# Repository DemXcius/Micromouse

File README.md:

# Micromouse
# The repository for a third-year engineering design project
This repository contains the design and production files for the Power and Sensor modules of a micro-mouse, as part of the EEE3088F course at UCT 2024 Main Project.

# Project Overview: Micro-Mouse Hardware Design

## What is a Micro-Mouse?
In essence, a micro-mouse is a maze-solving robot. If you're unfamiliar with the concept, watch [Veritasium's](https://www.youtube.com/watch?v=ZMQbHMgK2rw) video to gain a clearer understanding. It's worth noting that while the robots featured in the video may be quite speedy, this micro-mouse will likely (almost certainly) operate at a slower pace. Nonetheless, let the video serve as inspiration.

## Project Description
This project focuses primarily on the design of the micro-mouse's hardware, with some minor software components. The main challenge lies in meeting the project's requirements while adhering to a STRICT budget. To facilitate this endeavor, the project has been divided into four modules: the processor, motherboard, sensing, and power.
The processor and motherboard modules have already been designed and this repository focuses only on the sensing and power modules. 

## Project Modules

### Processor Module: 
This module entails the design of the microcontroller unit responsible for controlling the micro-mouse's actions within the maze. The processor used is an STM32L476.

### Motherboard Module: 
The motherboard serves as the central hub for connecting various hardware components of the micro-mouse. Here, there is leeway as to how the motherboard is designed.

### Sensing Module: 
The project will involve designing and manufacturing the sensing module, which comprises sensors responsible for detecting walls, corners, and other obstacles within the maze.

### Power Module: 
Lastly, the project involves designing and manufacturing the power module, which will provide the necessary electrical power to all components of the micro-mouse.

## Budget Constraint
It's crucial to note that this project had a strict budget constraint imposed. While innovation and creativity are encouraged, all design decisions were made with the budget in mind.

## Project Details:
- Project Focus: Power and sensing module design and manufacturing.
- Connectors: JST PH 2mm pin pitch connector for the battery and a 2x8 (2.54mm pin pitch) pin header for interfacing with the motherboard.
- Budget: $8.25 per board.

## Subsystem Description: Power
- Motor Operation: Controls 2 motors, each capable of drawing up to 200mA, powered by a 1S1P battery.
- Battery Voltage Sensing: Provides an analog connection to sense battery voltage for battery state of charge (SoC) monitoring.
- Battery Charging: Charges the battery from the 5V input pin. Must handle the scenario when 5V is removed.
- ON/OFF Switch: Incorporates an ON/OFF switch with specific power consumption requirements in the OFF and ON states.
  
## Subsystem Description: Sensing
- Sensor Operation: Detects whether there is an obstacle in front of the robot or on its sides.
- Power Saving: Has switching means to save power when not in operation.
- Main Components: 4x TSAL4400 IR LED's, 3x SFH205F photodiodes, 1x LiPo 800mAh 3.7V

- ## Included Files:
- Datasheets: Datasheets for components used in the Power and Sensing modules.
- Production Files: Files required for manufacturing the Power and Sensing module, including Gerber files and Bill of Materials (BOM).
- Schematics: Schematics for Power and Sensing modules.
  
## Usage:
- Clone the repository to access all project files.
- Review the datasheets for component specifications.
- Use the production files for manufacturing the Power or Sensing module PCB's.
- Review and modify the PCB files as needed for customization.
  
- NOTE: Production and files associated with the production were designed and used with [jlcpcb](https://jlcpcb.com/) as the manufacturer in mind.

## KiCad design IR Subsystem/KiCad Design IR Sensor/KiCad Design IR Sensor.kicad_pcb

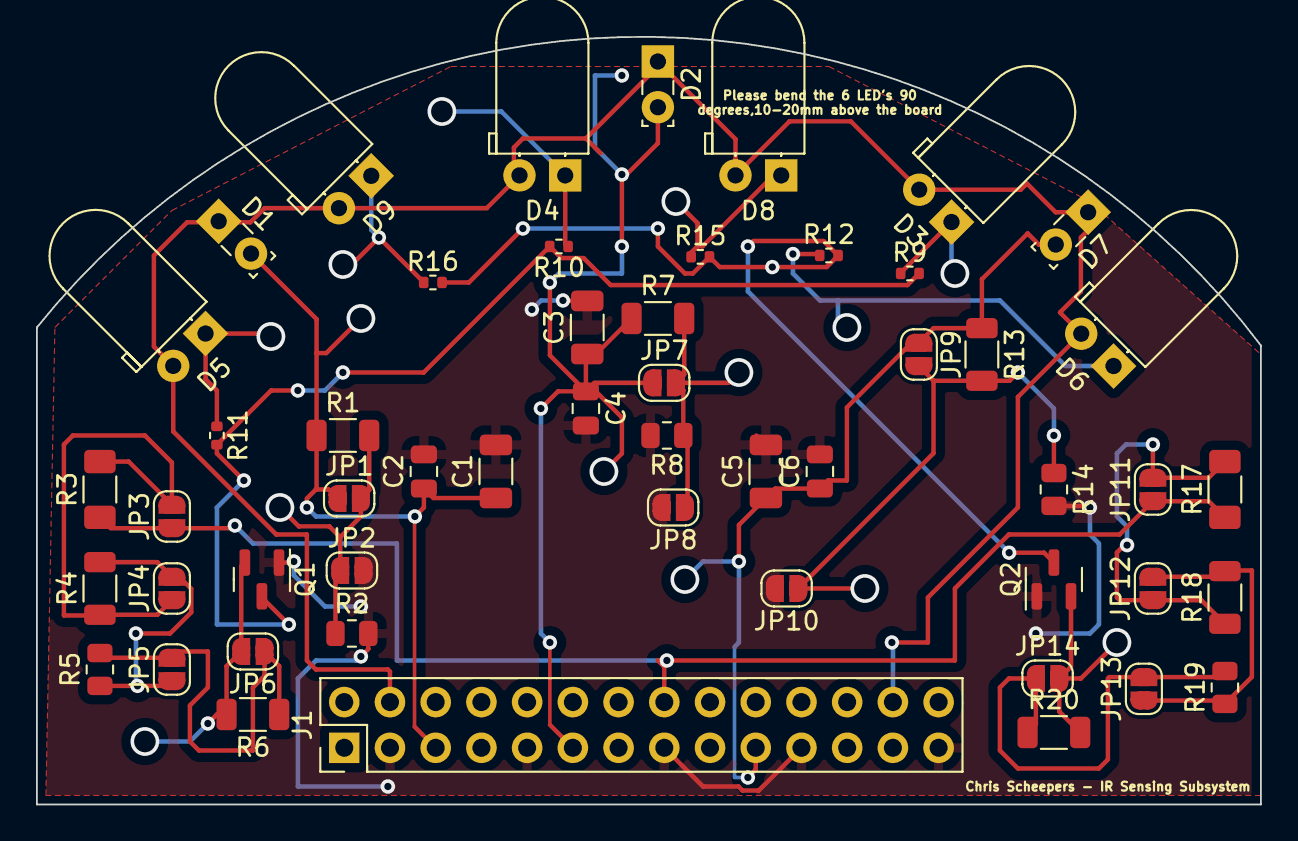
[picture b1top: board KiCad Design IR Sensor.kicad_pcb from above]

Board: 2 copper layers, 68.0 x 42.6 mm, 52 parts (0 on the bottom side), 25 nets.

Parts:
C1, C3, C5: 100nF; C_1206_3216Metric
C2, C4, C6: 4.7uF; C_0805_2012Metric
D1, D2, D7: SFH205F; LED_SideEmitter_Rectangular_W4.5mm_H1.6mm
D3, D4, D5, D6, D8, D9: TSAL4400; LED_D5.0mm_Horizontal_O1.27mm_Z3.0mm_IRBlack
J1: Conn_02x14_Odd_Even; PinHeader_2x14_P2.54mm_Vertical
JP1, JP2, JP3, JP4, JP5, JP6, JP7, JP8, JP9, JP10, JP11, JP12, JP13, JP14: SolderJumper_2_Open; SolderJumper-2_P1.3mm_Open_RoundedPad1.0x1.5mm
Q1, Q2: 2N2219; SOT-23
R1, R7, R13: 100k; R_1206_3216Metric
R2, R8, R14: 10k; R_0805_2012Metric
R3, R17: 100; R_1206_3216Metric_Pad1.30x1.75mm_HandSolder
R4, R18: 300; R_1206_3216Metric
R5, R19: 600; R_0805_2012Metric
R6, R20: 1000; R_1206_3216Metric
R9, R10, R11, R12, R15, R16: 22; R_0402_1005Metric

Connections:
+BATT: D1.1 (K), D2.1 (K), D3.2 (A), D4.2 (A), D5.2 (A), D6.2 (A), D7.1 (K), D8.2 (A), D9.2 (A), J1.4, J1.26
GND: C1.2, C2.2, C3.2, C4.2, C5.2, C6.2, J1.3, J1.9, J1.15, J1.21, J1.27, JP2.2 (B), JP8.2 (B), JP10.2 (B), Q1.1 (E), Q2.1 (E), R2.2, R8.2, R14.2
unnamed: D3.1 (K), R9.1
unnamed: D4.1 (K), R10.1
unnamed: D5.1 (K), R11.1
unnamed: D6.1 (K), R12.1
unnamed: D8.1 (K), R15.1
unnamed: D9.1 (K), R16.1
unnamed: JP1.2 (B), JP2.1 (A), R1.2, R2.1
unnamed: JP3.2 (B), JP4.1 (A), R3.2, R4.1
unnamed: JP4.2 (B), JP5.1 (A), R4.2, R5.1
unnamed: JP5.2 (B), JP6.1 (A), R5.2, R6.1
unnamed: JP6.2 (B), Q1.2 (B), R6.2
unnamed: JP7.2 (B), JP8.1 (A), R7.2, R8.1
unnamed: JP9.2 (B), JP10.1 (A), R13.2, R14.1
unnamed: JP11.2 (B), JP12.1 (A), R17.2, R18.1
unnamed: JP12.2 (B), JP13.1 (A), R18.2, R19.1
unnamed: JP13.2 (B), JP14.1 (A), R19.2, R20.1
unnamed: JP14.2 (B), Q2.2 (B), R20.2
unnamed: Q1.3 (C), R9.2, R10.2, R11.2
unnamed: Q2.3 (C), R12.2, R15.2, R16.2
PWM: J1.16, JP3.1 (A), JP11.1 (A), R3.1, R17.1
V_out_left: C1.1, C2.1, D1.2 (A), J1.5, JP1.1 (A), R1.1
V_out_mid: C3.1, C4.1, D2.2 (A), J1.11, JP7.1 (A), R7.1
V_out_right: C5.1, C6.1, D7.2 (A), J1.19, JP9.1 (A), R13.1

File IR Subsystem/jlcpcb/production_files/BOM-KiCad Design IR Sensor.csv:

Comment,Designator,Footprint,LCSC
10k,"R14,R2,R8",R_0805_2012Metric,C17414
4.7uF,"C2,C4,C6",C_0805_2012Metric,C1779
300,"R18,R4",R_1206_3216Metric,C17887
100k,"R1,R13,R7",R_1206_3216Metric,C17900
100,"R17,R3",R_1206_3216Metric_Pad1.30x1.75mm_HandSolder,C17901
2N2219,"Q1,Q2",SOT-23,C2146
100nF,"C1,C3,C5",C_1206_3216Metric,C24497
SFH205F,"D1,D2,D7",LED_SideEmitter_Rectangular_W4.5mm_H1.6mm,C2693588
22,"R10,R11,R12,R15,R16,R9",R_0402_1005Metric,C2759745
600,"R19,R5",R_0805_2012Metric,C28636
1000,"R20,R6",R_1206_3216Metric,C4410
TSAL4400,"D3,D4,D5,D6,D8,D9",LED_D5.0mm_Horizontal_O1.27mm_Z3.0mm_IRBlack,C94135
SolderJumper_2_Open,JP3,SolderJumper-2_P1.3mm_Open_RoundedPad1.0x1.5mm,
SolderJumper_2_Open,JP2,SolderJumper-2_P1.3mm_Open_RoundedPad1.0x1.5mm,
SolderJumper_2_Open,JP9,SolderJumper-2_P1.3mm_Open_RoundedPad1.0x1.5mm,
SolderJumper_2_Open,JP13,SolderJumper-2_P1.3mm_Open_RoundedPad1.0x1.5mm,
SolderJumper_2_Open,JP11,SolderJumper-2_P1.3mm_Open_RoundedPad1.0x1.5mm,
SolderJumper_2_Open,JP7,SolderJumper-2_P1.3mm_Open_RoundedPad1.0x1.5mm,
SolderJumper_2_Open,JP14,SolderJumper-2_P1.3mm_Open_RoundedPad1.0x1.5mm,
SolderJumper_2_Open,JP12,SolderJumper-2_P1.3mm_Open_RoundedPad1.0x1.5mm,
SolderJumper_2_Open,JP10,SolderJumper-2_P1.3mm_Open_RoundedPad1.0x1.5mm,
SolderJumper_2_Open,JP8,SolderJumper-2_P1.3mm_Open_RoundedPad1.0x1.5mm,
SolderJumper_2_Open,JP6,SolderJumper-2_P1.3mm_Open_RoundedPad1.0x1.5mm,
SolderJumper_2_Open,JP5,SolderJumper-2_P1.3mm_Open_RoundedPad1.0x1.5mm,
SolderJumper_2_Open,JP4,SolderJumper-2_P1.3mm_Open_RoundedPad1.0x1.5mm,
SolderJumper_2_Open,JP1,SolderJumper-2_P1.3mm_Open_RoundedPad1.0x1.5mm,
Conn_02x14_Odd_Even,J1,PinHeader_2x14_P2.54mm_Vertical,

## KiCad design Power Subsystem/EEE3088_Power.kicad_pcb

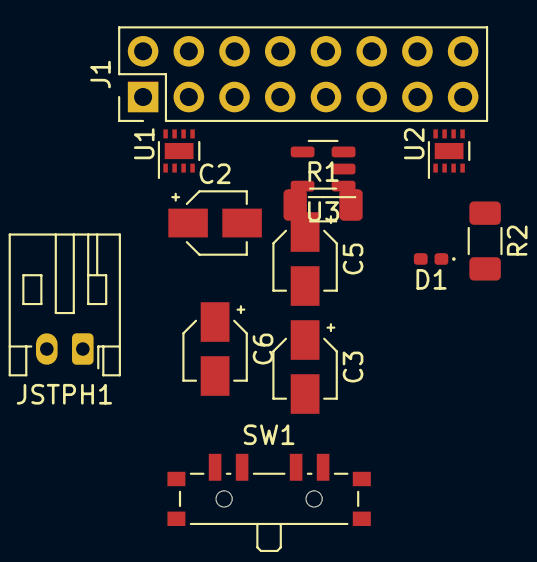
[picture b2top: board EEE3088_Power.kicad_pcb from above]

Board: 2 copper layers, 13 parts (0 on the bottom side), 16 nets, no tracks yet.

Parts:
C2, C3: 0.1u; CP_Elec_3x5.3
C5, C6: 4.7u; CP_Elec_3x5.3
D1: LED; D_0402_1005Metric_Pad0.77x0.64mm_HandSolder
J1: Conn_01x16_Male; PinHeader_2x08_P2.54mm_Vertical
JSTPH1: Conn_01x02_Female; JST_PH_S2B-PH-K_1x02_P2.00mm_Horizontal
R1: 2K; R_1206_3216Metric_Pad1.30x1.75mm_HandSolder
R2: 470; R_1206_3216Metric_Pad1.30x1.75mm_HandSolder
SW1: SW_SPDT; SW_SP3T_PCM13
U1, U2: DRV8837; WSON-8-1EP_2x2mm_P0.5mm_EP0.9x1.6mm
U3: MCP73831-2-OT; SOT-23-5

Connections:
/+5V: C5.1, D1.2 (A), J1.11, U3.4 (VDD)
/BATT1: J1.7, JSTPH1.1, SW1.2 (B)
/BATT2: J1.8, JSTPH1.2
/BATT+: C2.1, C3.1, C6.1, SW1.1 (A), U1.1 (VM), U1.7 (~SLEEP), U1.8 (VCC), U2.1 (VM), U2.7 (~SLEEP), U2.8 (VCC), U3.3 (VBAT)
/Motor1_A: J1.13, U2.2 (OUT1)
/Motor1_B: J1.15, U2.3 (OUT2)
/Motor2_A: J1.1, U1.2 (OUT1)
/Motor2_B: J1.3, U1.3 (OUT2)
/PC6: J1.2, U1.6 (IN1)
/PC7: J1.4, U1.5 (IN2)
/PC8: J1.14, U2.6 (IN1)
/PC9: J1.16, U2.5 (IN2)
GND: C2.2, C3.2, C5.2, C6.2, J1.5, J1.6, R1.2, SW1.3 (C), U1.4 (GND), U1.9 (GND), U2.4 (GND), U2.9 (GND), U3.2 (VSS)
unnamed: D1.1 (K), R2.2
unnamed: R1.1, U3.5 (PROG)
unnamed: R2.1, U3.1 (STAT)

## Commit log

2024-03-20 Create Datasheets
2024-03-24 PCB Design complete.
    Final upload to repo before submission of Gerber files.
2024-03-24 Deleted IR Sensor directory
    Uploading a new sub-directory after this.
2024-03-24 Create IR Subsystem
2024-03-24 Final Submission for PCB Design
2024-03-24 JLCPCB prod. files
    BOM, CPL and Gerber Files
2024-04-09 Changed IR Sensor Section Format
2024-04-09 Formatting
2024-04-09 moved .gitignore
2024-04-09 Removed KiCad Design IR Sensor-backups
2024-04-09 Create Datasheets Directory
2024-04-09 Uploaded IR Subsytem Schematic
2024-04-17 Create Gerbers
